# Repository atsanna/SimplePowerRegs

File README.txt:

This is the Simple Power series of switching regulators,
and its Open Source Hardware OSHW documentation.

They were designed in this order, making changes and improvements
along the way. pwrlnk.com has a blog with some discussion of the 
design process.

v1 
is 5V 3A output, with up to 30VDC input.
still useful for smaller loads.

v2 
changes the switcher part to 5 Amp output and adds a full-wave 
bridge at the input, up to 7-28VDC or 6-18VAC.

The same board supports two variations with a few parts changes:
1) 5Amp fixed 5VDC output.
2) 5Amp varible 1.2 ~ 15 VDC output.

v3 
is 5V 5A output, with 7-28VDC or 6-18VAC input.

v4 
is a refinement of v3, available at tindie.com

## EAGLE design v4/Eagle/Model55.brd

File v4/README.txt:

v4:

This version is a refinement of v3, also fixed 5V with 2 USB charge ports. 

It has a 5.5mm/2.1mm barrel connector on the input, and pads for bare wires
up to 16 AWG on input and output.

The board is compatible with 1cmg.net, 48mm (1.89") square with 3.2mm (1/8") 
mounting holes on 40mm (1.575") centers, suitable for 4-40 or M3 screws.

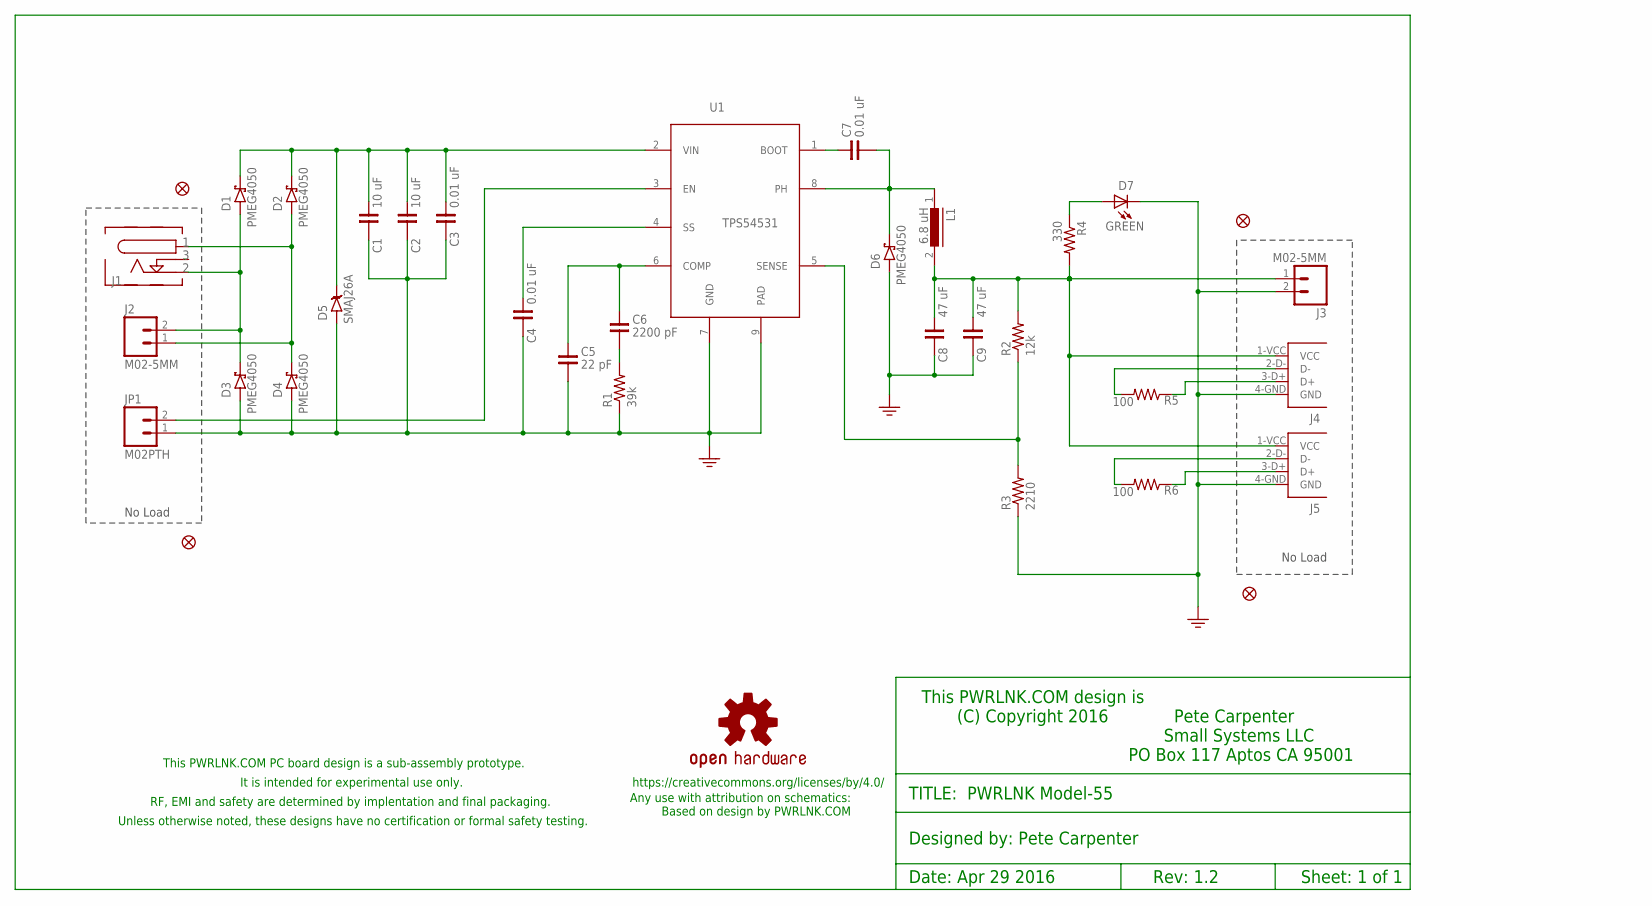
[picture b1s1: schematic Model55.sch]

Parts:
C1, C2: 10 uF; 1210
C3, C4, C7: 0.01 uF; 0805
C5: 22 pF; 0603
C6: 2200 pF; 0805
C8, C9: 47 uF; C1206
D1, D2, D3, D4, D6: PMEG4050EP; SOD128
D5: SMAJ26A; DO214BA
D7: GREEN; LED-0603
FID1, FID2, FID3, FID4: FIDUCIAL1X2; FIDUCIAL-1X2
J1: PJ-102AH
J2, J3: M02-5MM; SCREWTERMINAL-5MM-2
J4, J5: 87520; 87520-USB-A-FEMALE
JP1: M02PTH; 1X02
L1: 6.8 uH; DR125
LOGO1: OSHW-LOGOL; OSHW-LOGO-L
R1: 39k; 0603-RES
R2: 12k; 0603-RES
R3: 2210; 0603-RES
R4: 330; 0603-RES
R5, R6: 100; 0603-RES
U1: TPS54531; SOIC127P600X170-9N

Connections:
5V: C8.1, C9.1, J3.1, J4.1-VCC (VCC), J5.1-VCC (VCC), L1.2, R2.2, R4.2
AC1: D1.P$1A, D3.P$2C, J1.P$2 (2), J2.2
AC2: D2.P$1A, D4.P$2C, J1.P$1 (1), J2.1
BOOT: C7.1, U1.1 (BOOT)
COMP: C5.1, C6.1, U1.6 (COMP)
D+: J5.3-D+ (D+), R6.1
D+1: J4.3-D+ (D+), R5.1
D-: J5.2-D- (D-), R6.2
D-1: J4.2-D- (D-), R5.2
ENABLE: JP1.2, U1.3 (EN)
GND: C1.2, C2.2, C3.2, C4.2, C5.2, C8.2, C9.2, D3.P$1A, D4.P$1A, D5.A (P$1A), D6.P$1A, D7.C, J3.2, J4.4-GND (GND), J5.4-GND (GND), JP1.1, R1.1, R3.1, U1.7 (GND), U1.9 (PAD)
unnamed: C6.2, R1.2
PWRON: D7.A, R4.1
SENSE: R2.1, R3.2, U1.5 (SENSE)
SLOW: C4.1, U1.4 (SS)
VIN: C1.1, C2.1, C3.1, D1.P$2C, D2.P$2C, D5.C (P$2C), U1.2 (VIN)
VSW: C7.2, D6.P$2C, L1.1, U1.8 (PH)

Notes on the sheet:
No Load
Designed by: Pete Carpenter
This PWRLNK.COM design is (C) Copyright 2016 Pete Carpenter Small Systems LLC PO Box 117 Aptos CA 95001
TITLE: PWRLNK Model-55
Sheet: 1 of 1
Date: Apr 29 2016
Rev: 1.2
This PWRLNK.COM PC board design is a sub-assembly prototype.
RF, EMI and safety are determined by implentation and final packaging.
Unless otherwise noted, these designs have no certification or formal safety testing.
It is intended for experimental use only.
https://creativecommons.org/licenses/by/4.0/
Any use with attribution on schematics: Based on design by PWRLNK.COM

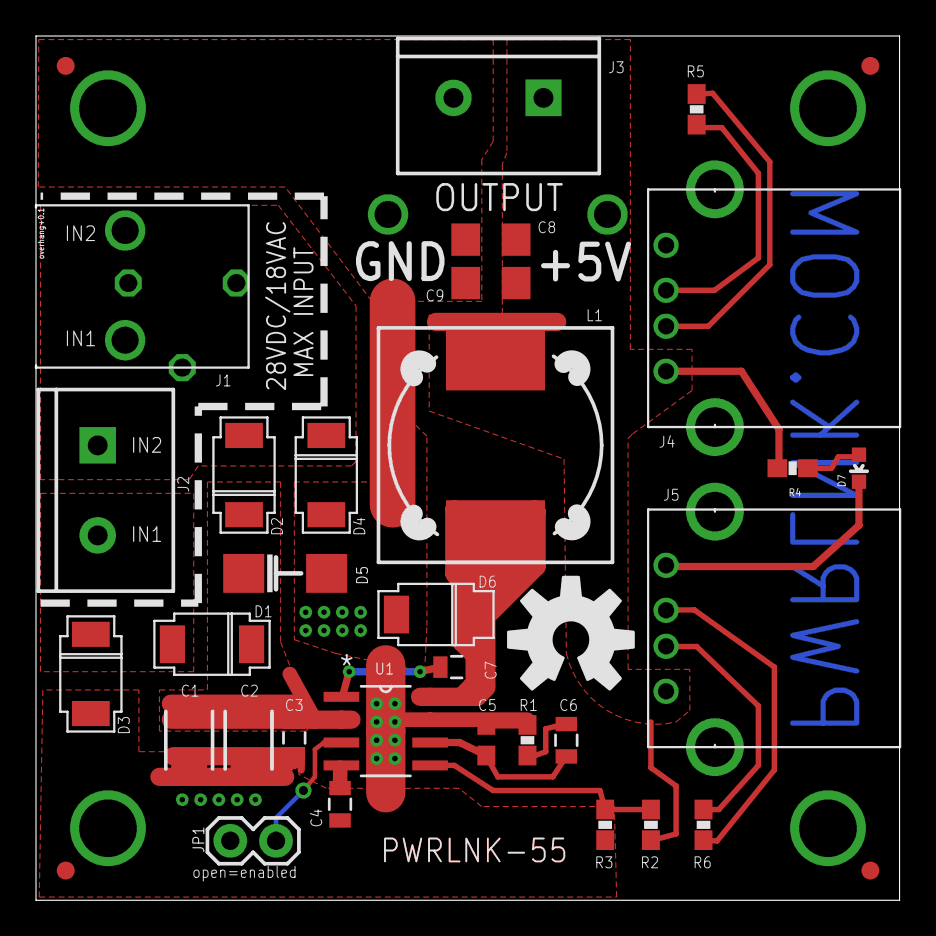
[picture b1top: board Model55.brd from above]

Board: 2 copper layers, 48.0 x 48.0 mm, 35 parts (0 on the bottom side), 17 nets.

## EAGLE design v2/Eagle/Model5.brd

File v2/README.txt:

v2:
This is a one board, two products design with both 5 Volt and 
adjustable voltage output, up to 5 Amps. Only a few parts are 
different between the two models.

See http://pwrlnk.com/?q=node/6

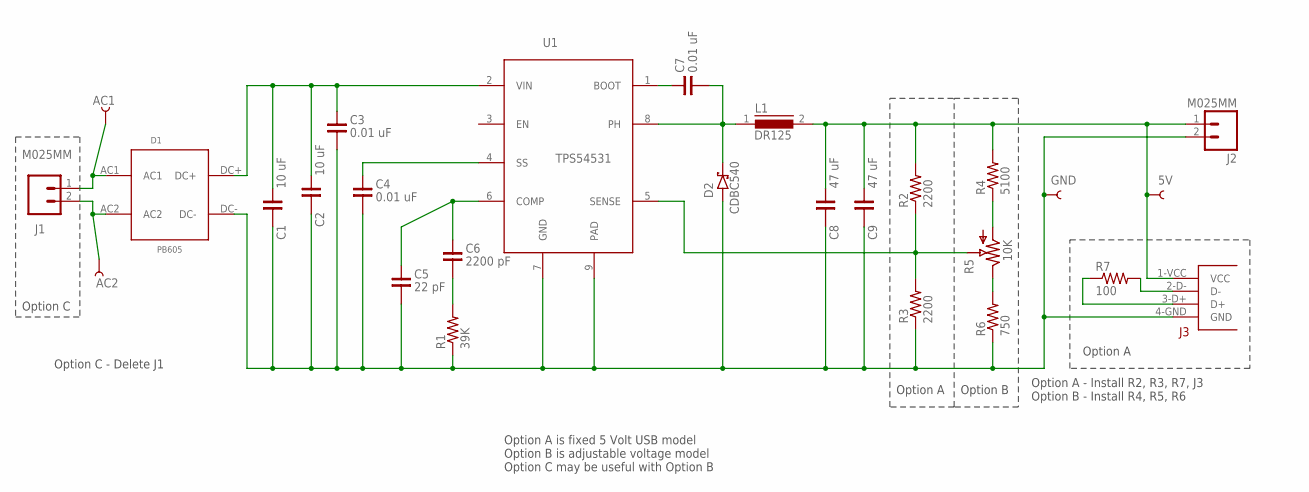
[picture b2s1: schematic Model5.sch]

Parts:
5V: TEST-POINT3; PAD.03X.03
AC1, AC2: TEST-POINT3; PAD.03X.03
C1, C2: 10 uF; 1210
C3, C4, C7: 0.01 uF; 0805
C5: 22 pF; 0805
C6: 2200 pF; 0805
C8, C9: 47 uF; C1206
D1: PB605; QUAD4PIN
D2: CDBC540; DO214AB
GND: TEST-POINT3; PAD.03X.03
J1, J2: M025MM; SCREWTERMINAL-5MM-2
JP3: 87520-USB-A-FEMALE
L1: DR125
R1: 39K; R0805
R2, R3: 2200; R0805
R4: 5100; R0805
R5: 3214J
R6: 750; R0805
R7: 100; R0805
U1: TPS54531; SOIC127P600X170-9N

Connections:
5V: 5V.P$1, C8.1, C9.1, J2.1, JP3.1-VCC (VCC), L1.2, R2.2, R4.2
AC1: AC1.P$1, D1.AC1, J1.1
AC2: AC2.P$1, D1.AC2, J1.2
BOOT: C7.1, U1.1 (BOOT)
COMP: C5.1, C6.1, U1.6 (COMP)
D+: JP3.3-D+ (D+), R7.1
D-: JP3.2-D- (D-), R7.2
GND: C1.2, C2.2, C3.2, C4.2, C5.2, C8.2, C9.2, D1.DC-, D2.ANODE, GND.P$1, J2.2, JP3.4-GND (GND), R1.1, R3.1, R6.1, U1.7 (GND), U1.9 (PAD)
unnamed: C6.2, R1.2
unnamed: R4.1, R5.P$1 (1)
unnamed: R5.P$3 (3), R6.2
SENSE: R2.1, R3.2, R5.P$2 (2), U1.5 (SENSE)
SLOW: C4.1, U1.4 (SS)
VIN: C1.1, C2.1, C3.1, D1.DC+, U1.2 (VIN)
VSW: C7.2, D2.CATHODE, L1.1, U1.8 (PH)

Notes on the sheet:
Option A - Install R2, R3, R7, J3 Option B - Install R4, R5, R6
Option A
Option B
Option C
Option C - Delete J1
Option A is fixed 5 Volt USB model Option B is adjustable voltage model Option C may be useful with Option B

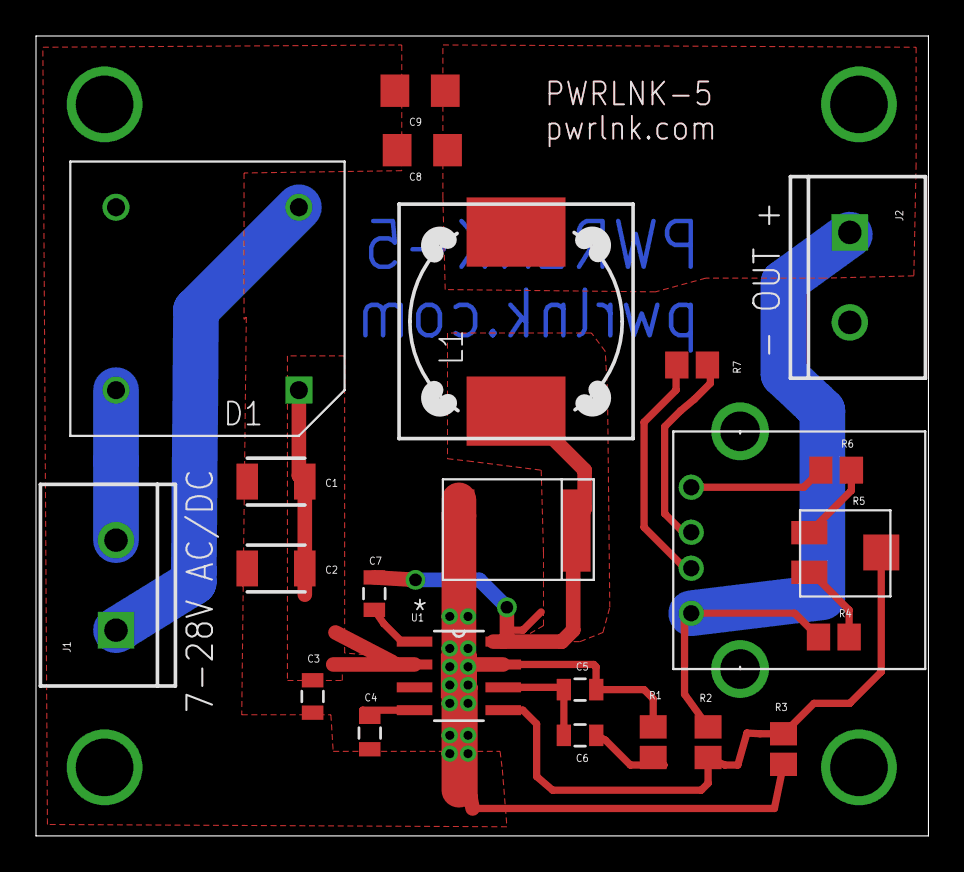
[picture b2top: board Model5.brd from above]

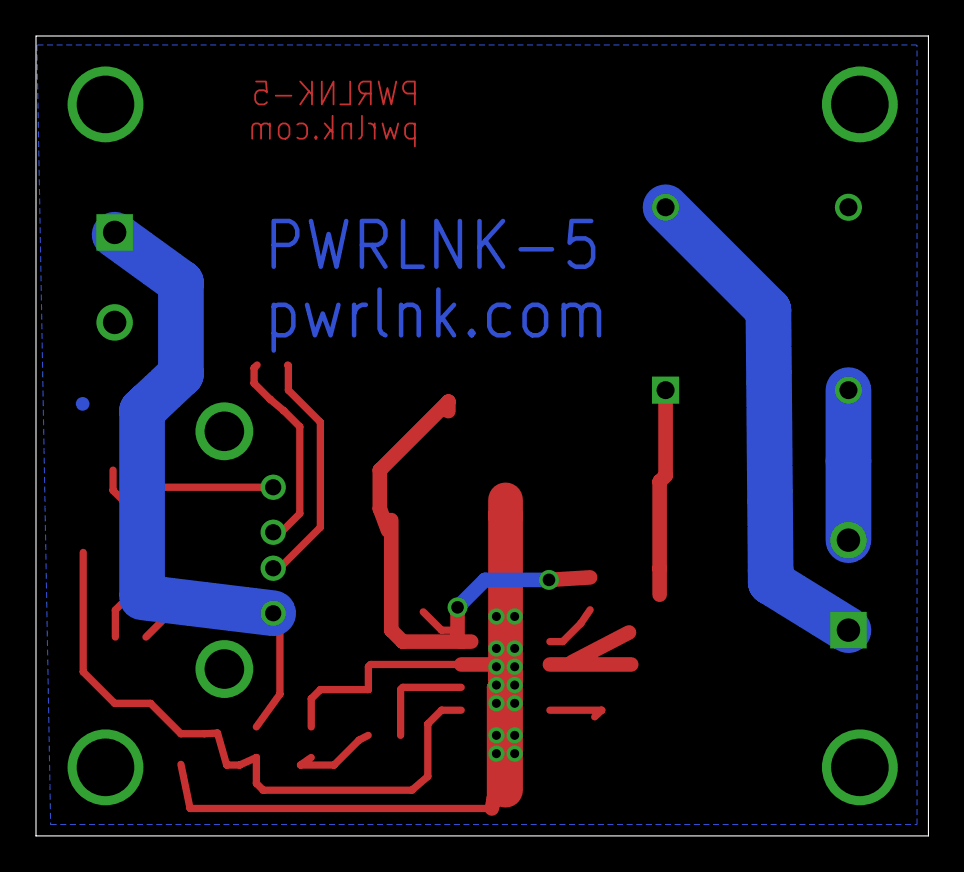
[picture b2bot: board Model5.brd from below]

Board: 2 copper layers, 49.6 x 44.4 mm, 27 parts (4 on the bottom side), 15 nets.

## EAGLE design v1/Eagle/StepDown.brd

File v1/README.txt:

v1:
This is fixed 5V output up to 3 Amps. I used the design process 
in the TI data sheet, so my own value added here is in the 
board layout. The full ground plane acts as a heatsink, so no
external heat sink should be needed.

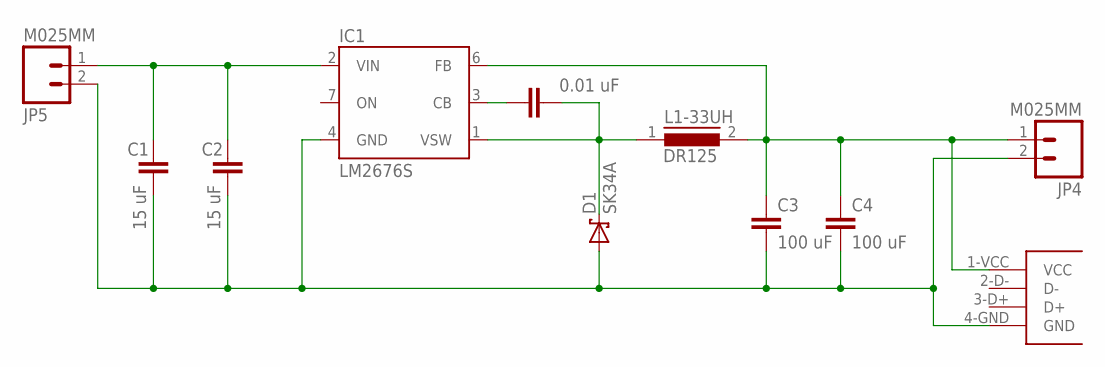
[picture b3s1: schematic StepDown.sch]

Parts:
C1, C2: 15 uF; C1210
C3, C4: 100 uF; C1210
C6: 0.01 uF; 0805
D1: SK34A; DO214AA
IC1: LM2676S; TO263-7
JP4, JP5: M025MM; SCREWTERMINAL-5MM-2
L1-33UH: DR125
U$1: 87520-USB-A-FEMALE

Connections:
5V: C3.1, C4.1, IC1.6 (FB), JP4.1, L1-33UH.2, U$1.1-VCC (VCC)
CB: C6.1, IC1.3 (CB)
GND: C1.2, C2.2, C3.2, C4.2, D1.A, IC1.4 (GND), JP4.2, JP5.2, U$1.4-GND (GND)
VIN: C1.1, C2.1, IC1.2 (VIN), JP5.1
VSW: C6.2, D1.C, IC1.1 (VSW), L1-33UH.1

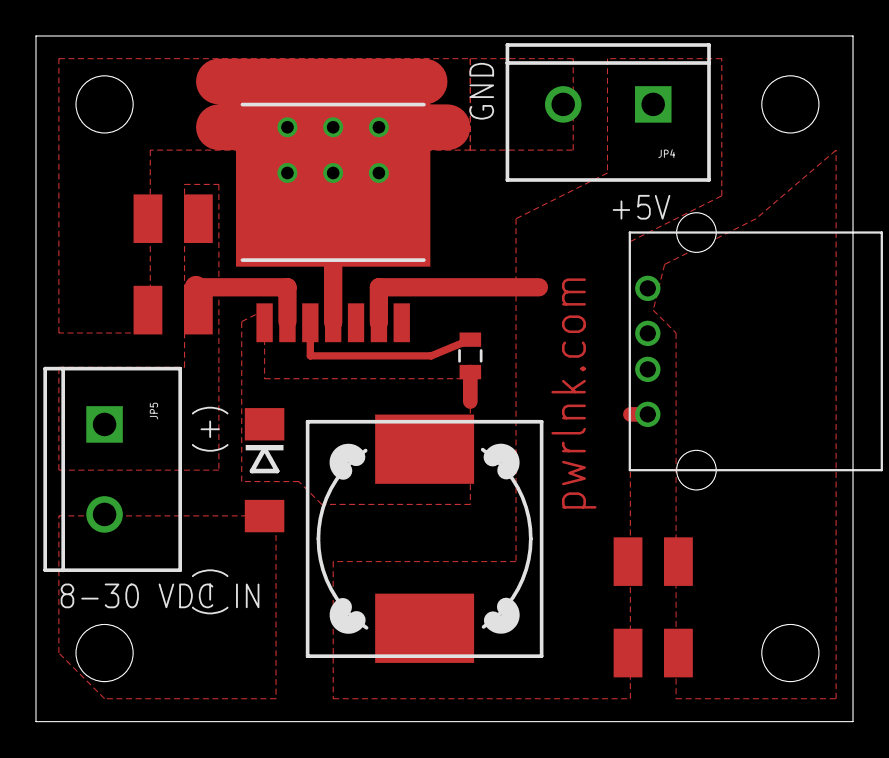
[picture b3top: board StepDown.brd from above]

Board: 2 copper layers, 45.4 x 38.1 mm, 11 parts (0 on the bottom side), 5 nets.

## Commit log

2014-10-14 :lollipop: Added .gitattributes & .gitignore files
2014-10-14 SimplePower setup
    READMEs for top and individual board directories.
2014-12-27 Eagle files, parts list, picture
2015-03-09 Update v2 details
    added eagle files, some pictures, parts list
2016-03-05 version 3
    5 Volts only, with surface mount bridge and TVS diode.
2016-03-24 update READMEs
2016-12-05 Added v4
    This is the release of version 4.

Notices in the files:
parts and their libraries:
SparkFun-Connectors: Licensing: Creative Commons ShareAlike 4.0 International - https://creativecommons.org/licenses/by-sa/4.0
